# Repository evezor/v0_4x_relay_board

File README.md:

# 4x Relay Board
*please note this board has been deprecated.

An edge board containing qty(4) 10 amp relays and qty(4) tactile buttons

source files can be found here: https://github.com/evezor/v0_4x_relay_board

This board uses the Evezor Stamp STMF405 MCU

source: https://github.com/evezor/Evezor-Stamp-STMF405

Evezor® and all associated marks, logos, and designs are registered trademarks and protected by copyright. Unauthorized use or reproduction of these trademarks and copyrighted materials is strictly prohibited.

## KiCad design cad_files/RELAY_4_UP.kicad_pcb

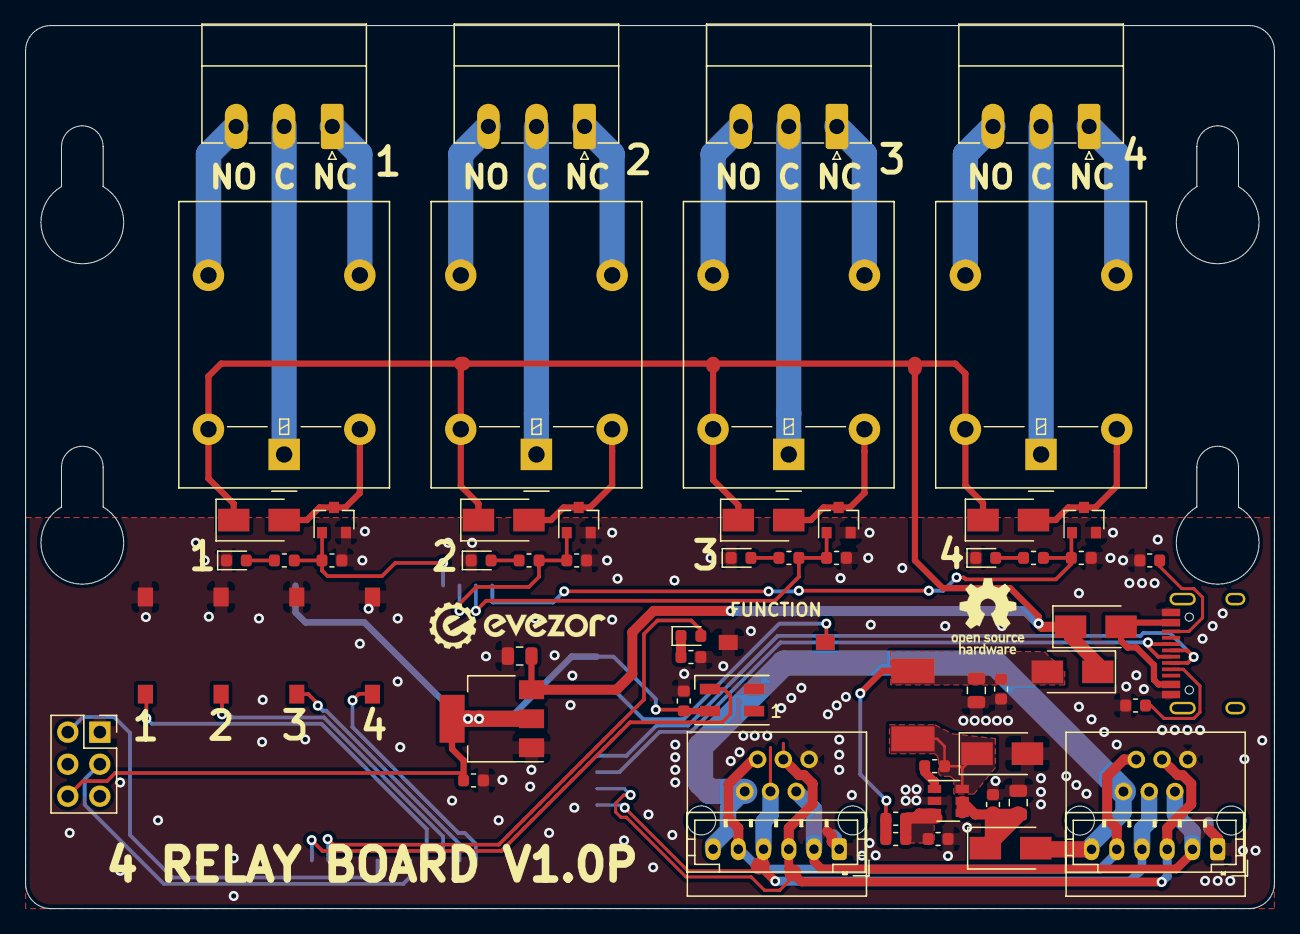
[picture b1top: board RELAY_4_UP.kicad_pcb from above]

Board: 2 copper layers, 99.0 x 70.0 mm, 63 parts (1 on the bottom side), 52 nets.

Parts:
C1, C2, C3, C5, C10: .1uF; C_0603_1608Metric
C4: 4.7uF; C_0805_2012Metric
C6: 22uF; C_0805_2012Metric
C8: 10uF; C_0805_2012Metric
C9: C_Small; C_0603_1608Metric
D1, D2, D4, D5: SX35_SCHOTTKY; D_SMA
D3, D7, D8, D9, D10: LED; LED_0603_1608Metric
D6: SK6812MINI; LED_SK6812MINI_PLCC4_3.5x3.5mm_P1.75mm
D11, D12, D13, D14: D; D_SMA
J1: USB_C_Receptacle_USB2.0; USB_C_Receptacle_HRO_TYPE-C-31-M-12
J2, J3: RJ11; RJ11_C189747_Horizontal
J4, J5: PH; JST_PH_B6B-PH-K_1x06_P2.00mm_Vertical
J6: Conn_02x03_Odd_Even; PinSocket_2x03_P2.54mm_Vertical
J7, J8, J9, J10: Conn_01x03; PhoenixContact_MC_1,5_3-G-3.81_1x03_P3.81mm_Horizontal
K1, K2, K3, K4: G5LE-1; Relay_SPDT_Omron-G5LE-1
L1: 22uH; INDUCTOR_7.5X6.6_GCDA0630-220MC
Q1, Q2, Q3, Q4: T2N7002BK,LM‎; SOT-23
R1, R5: 15k; R_0603_1608Metric
R2: 82k; R_0603_1608Metric
R3, R4: 5.1k; R_0603_1608Metric
R8, R10, R12, R14: 1k; R_0603_1608Metric
R9, R11, R13, R15: 10k; R_0603_1608Metric
SW1, SW2, SW3, SW4, SW5: SW_Push; SWITCH_2x3_SMD_TACTILE_GREEN
U1: SY8401ABC; SOT-23-6
U2: AMS1117-3.3; SOT-223-3_TabPin2
U3: EDGE_STM32F405_CPU_V1; EDGE_STAMP

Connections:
+3V3: C9.2, C10.1, D6.4, J6.6, U2.2, U3.1, U3.18
/BOOT: J6.3, U3.36
/BUTTON_A: SW2.1, U3.35
/BUTTON_B: SW3.1, U3.34
/BUTTON_C: SW4.1, U3.33
/BUTTON_D: SW5.1, U3.32
/CAN_H: J2.3, J3.3, J4.3, J5.3, U3.26
/CAN_L: J2.4, J3.4, J4.4, J5.4, U3.27
/CC1: J1.A5, R4.1
/CC2: J1.B5, R3.1
/D+: J1.A6, J1.B6, U3.25
/D-: J1.A7, J1.B7, U3.24
/FD_H: J2.2, J3.2, J4.2, J5.2
/FD_L: J2.5, J3.5, J4.5, J5.5
/FUNCTION_BUTTON: SW1.1, U3.20
/HBT_LED: D3.2, U3.41
/NEO_STATUS: D6.3, U3.42
/RELAY_1: Q4.1, R14.1, R15.2, U3.10
/RELAY_2: Q3.1, R12.1, R13.2, U3.11
/RELAY_3: Q2.1, R10.1, R11.2, U3.12
/RELAY_4: Q1.1, R8.1, R9.2, U3.13
/RESET: J6.2, U3.38
/USB_VCC: D4.2, J1.A4, J1.A9, J1.B4, J1.B9
/VREG_OUT: C8.1, D4.1, D5.1, D11.1, D12.1, D13.1, D14.1, K1.5, K2.5, K3.5, K4.5, U2.3
GND: C3.2, C4.2, C5.2, C6.2, C8.2, C9.1, C10.2, D1.2, D6.2, D7.1, D8.1, D9.1, D10.1, J1.A1, J1.A12, J1.B1, J1.B12, J2.1, J3.1, J4.1, J5.1, J6.1, Q1.2, Q2.2, Q3.2, Q4.2, R1.1, R3.2, R4.2, R5.1, R9.1, R11.1, R13.1, R15.1, SW1.2, SW2.2, SW3.2, SW4.2, SW5.2, U1.2, U2.1, U3.2, U3.17, U3.43
unnamed: C1.1, D1.1, L1.1, U1.6
unnamed: C1.2, U1.1
unnamed: C2.1, C5.1, C6.1, D5.2, L1.2, R2.1
unnamed: C2.2, R1.2, R2.2, U1.3
unnamed: C3.1, C4.1, D2.1, U1.4, U1.5
unnamed: D3.1, R5.2
unnamed: D7.2, R8.2
unnamed: D8.2, R10.2
unnamed: D9.2, R12.2
unnamed: D10.2, R14.2
unnamed: D11.2, K1.2, Q1.3
unnamed: D12.2, K3.2, Q3.3
unnamed: D13.2, K4.2, Q4.3
unnamed: D14.2, K2.2, Q2.3
unnamed: J7.1, K1.3
unnamed: J7.2, K1.1
unnamed: J7.3, K1.4
unnamed: J8.1, K2.3
unnamed: J8.2, K2.1
unnamed: J8.3, K2.4
unnamed: J9.1, K3.3
unnamed: J9.2, K3.1
unnamed: J9.3, K3.4
unnamed: J10.1, K4.3
unnamed: J10.2, K4.1
unnamed: J10.3, K4.4
VBUS: D2.2, J2.6, J3.6, J4.6, J5.6

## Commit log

2023-09-11 add pics
